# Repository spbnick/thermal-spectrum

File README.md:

Thermal Spectrum
================
Thermal Spectrum is a ZX Printer interface to a thermal printer module, for ZX
Spectrum computer.

[![Development setup][development_setup_thumb]][development_setup]

Building the firmware
---------------------
First you'll need the compiler. If you're using a Debian-based Linux you can
get it by installing `gcc-arm-none-eabi` package. Then you'll need the
[libstammer][libstammer] library. Build it first, then export environment
variables pointing to it:

    export CFLAGS=-ILIBSTAMMER_DIR LDFLAGS=-LLIBSTAMMER_DIR

`LIBSTAMMER_DIR` above is the directory where libstammer build is located.

After that you can build the firmware using `make`.

[development_setup_thumb]: development_setup.thumb.jpg
[development_setup]: development_setup.jpg
[libstammer]: https://github.com/spbnick/libstammer

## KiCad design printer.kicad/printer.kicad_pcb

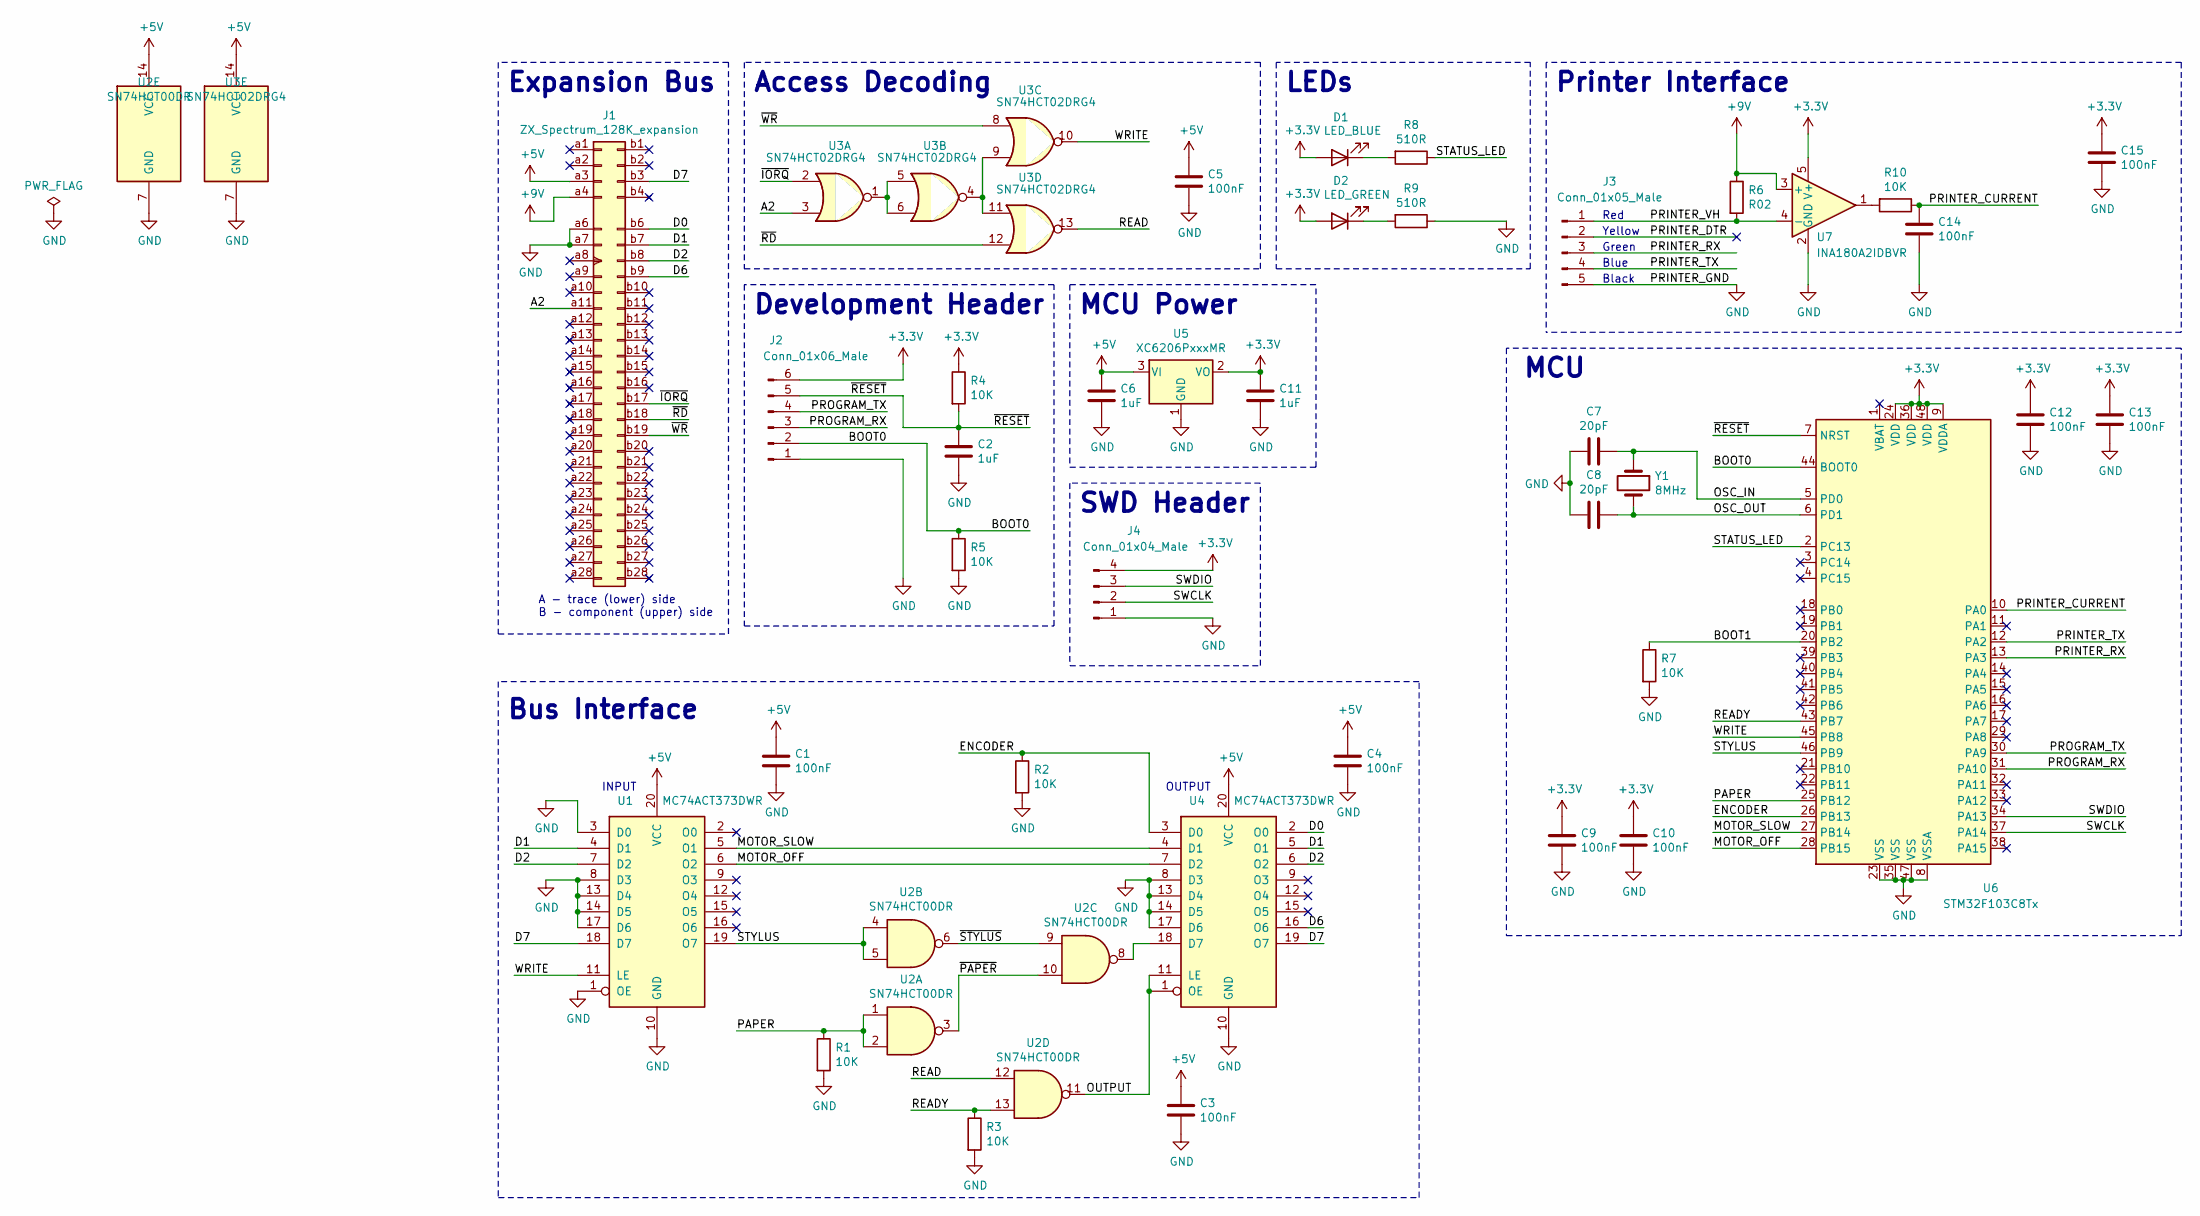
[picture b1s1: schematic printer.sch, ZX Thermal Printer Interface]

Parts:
C1, C3, C4, C5, C9, C10, C12, C13, C14, C15: 100nF; C_0603_1608Metric; LCSC C24452
C2, C6, C11: 1uF; C_0603_1608Metric; LCSC C15849
C7, C8: 20pF; C_0603_1608Metric; LCSC C1648
D1: LED_BLUE; LED_0603_1608Metric; LCSC C72041
D2: LED_GREEN; LED_0603_1608Metric; LCSC C72043
J1: ZX_Spectrum_128K_expansion; board_socket
J2: Conn_01x06_Male; PinHeader_1x06_P2.54mm_Vertical
J3: Conn_01x05_Male; JST_XH_B5B-XH-A_1x05_P2.50mm_Vertical
J4: Conn_01x04_Male; PinHeader_1x04_P2.54mm_Vertical
R1, R2, R3, R4, R5, R7: 10K; R_0603_1608Metric; LCSC C25804
R6: R02; R_1206_3216Metric; LCSC C83318
R8, R9: 510R; R_0603_1608Metric; LCSC C23193
R10: 10K; R_0603_1608Metric; LCSC C23193
U1, U4: MC74ACT373DWR; SOIC-20W_7.5x12.8mm_P1.27mm; LCSC C233456
U2: SN74HCT00DR; SOIC-14_3.9x8.7mm_P1.27mm; LCSC C6764
U3: SN74HCT02DRG4; SOIC-14_3.9x8.7mm_P1.27mm; LCSC C6765
U5: XC6206PxxxMR; SOT-23; LCSC C5446
U6: STM32F103C8Tx; LQFP-48_7x7mm_P0.5mm; LCSC C8734
U7: INA180A2IDBVR; SOT-23-5; LCSC C192764
Y1: 8MHz; Crystal_SMD_5032-2Pin_5.0x3.2mm; LCSC C156253

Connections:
+3V3: C9.1, C10.1, C11.2, C12.1, C13.1, C15.1, D1.2 (A), D2.2 (A), J2.6, J4.4, R4.1, U5.2 (VO), U6.9 (VDDA), U6.24 (VDD), U6.36 (VDD), U6.48 (VDD), U7.5 (V+)
+5V: C1.1, C3.1, C4.1, C5.1, C6.2, J1.a3 (+5V), U1.20 (VCC), U2.14 (VCC), U3.14 (VCC), U4.20 (VCC), U5.3 (VI)
+9V: J1.a4 (+9V), R6.1, U7.3 (+)
/A2: J1.a11 (A2), U3.3
/BOOT0: J2.2, R5.1, U6.44 (BOOT0)
/BOOT1: R7.1, U6.20 (PB2)
/D0: J1.b6 (D0), U4.2 (O0)
/D1: J1.b7 (D1), U1.4 (D1), U4.5 (O1)
/D2: J1.b8 (D2), U1.7 (D2), U4.6 (O2)
/D6: J1.b9 (D6), U4.16 (O6)
/D7: J1.b3 (D7), U1.18 (D7), U4.19 (O7)
/ENCODER: R2.1, U4.3 (D0), U6.26 (PB13)
/MOTOR_OFF: U1.6 (O2), U4.7 (D2), U6.28 (PB15)
/MOTOR_SLOW: U1.5 (O1), U4.4 (D1), U6.27 (PB14)
/OSC_IN: C7.1, U6.5 (PD0), Y1.1
/OSC_OUT: C8.1, U6.6 (PD1), Y1.2
/OUTPUT: U2.11, U4.1 (OE), U4.11 (LE)
/PAPER: R1.1, U2.1, U2.2, U6.25 (PB12)
/PRINTER_CURRENT: C14.1, R10.1, U6.10 (PA0)
/PRINTER_DTR: J3.2
/PRINTER_RX: J3.3, U6.13 (PA3)
/PRINTER_TX: J3.4, U6.12 (PA2)
/PRINTER_VH: J3.1, R6.2, U7.4 (-)
/PROGRAM_RX: J2.3, U6.31 (PA10)
/PROGRAM_TX: J2.4, U6.30 (PA9)
/READ: U2.12, U3.13
/READY: R3.1, U2.13, U6.43 (PB7)
/STATUS_LED: R8.1, U6.2 (PC13)
/STYLUS: U1.19 (O7), U2.4, U2.5, U6.46 (PB9)
/SWCLK: J4.2, U6.37 (PA14)
/SWDIO: J4.3, U6.34 (PA13)
/WRITE: U1.11 (LE), U3.10, U6.45 (PB8)
/~IORQ: J1.b17 (~IORQ), U3.2
/~PAPER: U2.3, U2.10
/~RD: J1.b18 (~RD), U3.12
/~RESET: C2.2, J2.5, R4.2, U6.7 (NRST)
/~STYLUS: U2.6, U2.9
/~WR: J1.b19 (~WR), U3.8
GND: C1.2, C2.1, C3.2, C4.2, C5.2, C6.1, C7.2, C8.2, C9.2, C10.2, C11.1, C12.2, C13.2, C14.2, C15.2, J1.a6 (0V), J1.a7 (0V), J2.1, J3.5, J4.1, R1.2, R2.2, R3.2, R5.2, R7.2, R9.1, U1.1 (OE), U1.3 (D0), U1.8 (D3), U1.10 (GND), U1.13 (D4), U1.14 (D5), U1.17 (D6), U2.7 (GND), U3.7 (GND), U4.8 (D3), U4.10 (GND), U4.13 (D4), U4.14 (D5), U4.17 (D6), U5.1 (GND), U6.8 (VSSA), U6.23 (VSS), U6.35 (VSS), U6.47 (VSS), U7.2 (GND)
unnamed: D1.1 (K), R8.2
unnamed: D2.1 (K), R9.2
unnamed: R10.2, U7.1
unnamed: U2.8, U4.18 (D7)
unnamed: U3.1, U3.5, U3.6
unnamed: U3.4, U3.9, U3.11

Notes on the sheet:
A - trace (lower) side B - component (upper) side
INPUT
OUTPUT
Access Decoding
Development Header
Bus Interface
MCU Power
LEDs
SWD Header
MCU
Expansion Bus
Printer Interface
Red
Yellow
Green
Blue
Black

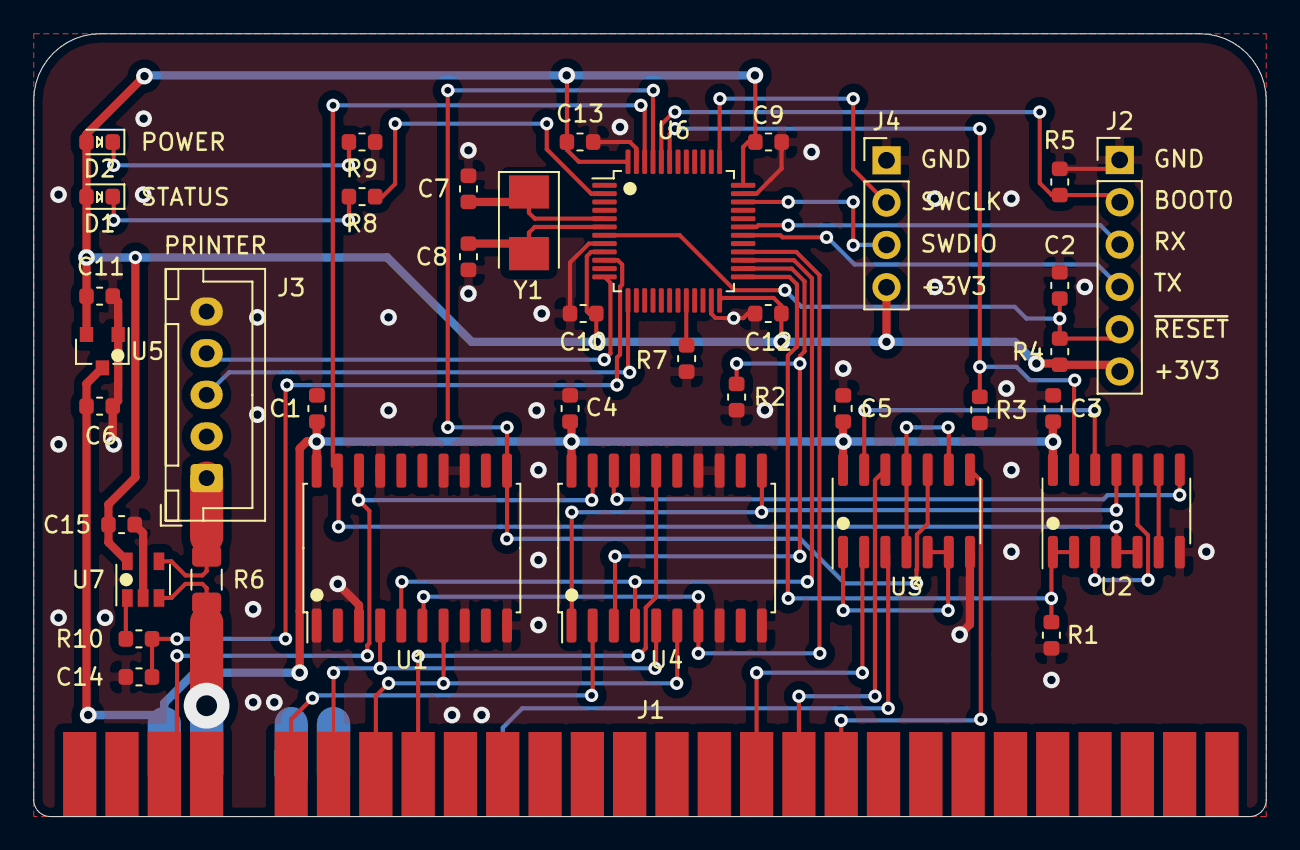
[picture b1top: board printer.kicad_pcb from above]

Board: 2 copper layers, 74.0 x 47.0 mm, 39 parts (0 on the bottom side), 44 nets.

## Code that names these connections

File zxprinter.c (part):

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{
    /* Read the pins */
    uint16_t pins = zxprinter_gpio->idr;
    uint16_t motor_off = (pins >> ZXPRINTER_PIN_MOTOR_OFF) & 1U;
    uint16_t motor_slow = (pins >> ZXPRINTER_PIN_MOTOR_SLOW) & 1U;
    /* Determine current and next clock step and level */
    uint32_t clock_level = zxprinter_clock_level;
    uint32_t next_clock_step = zxprinter_clock_step + 1;
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                            ZXPRINTER_CYCLE_MARGIN_STEPS);
            uint8_t byte = dot >> 3;
            uint8_t bit = 7 - (dot & 0x7);
            uint8_t stylus = ((pins >> ZXPRINTER_PIN_STYLUS) & 1);
            /* Record dot state */
            zxprinter_line_buf[byte] =
                (zxprinter_line_buf[byte] & ~(1 << bit)) |
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
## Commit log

2018-05-27 Add basic Makefile and dummy program
2018-05-27 Add draft serial IO
2018-05-27 Add .gitignore
2018-05-27 Rename serial_tx_ functions to serial_tx_buf_
2018-10-03 Improve wording of circular buffer description
2018-11-25 Makefile: Include dependencies
2018-11-25 Makefile: Move default target to the front
2018-11-25 Add serial module
2018-12-02 Add printer interface module
2018-12-02 Rename program to ts (thermal spectrum)
2018-12-02 Implement printing a test image on power-on
2018-12-03 Add KiCAD schematics
2018-12-03 Add README.md
2018-12-03 README.md: Refine introduction
2018-12-03 README.md: Move links to the back
2018-12-03 README.md: Fix libstammer link
2019-01-06 Reimplement ZX Spectrum bus interface
2019-01-06 Add draft ZX Printer bus interface implementation
2019-01-06 Remove trailing whitespace from zxprinter.c
2019-01-06 Add notes.txt
2019-08-17 Redo latching in HW, understand interface better
    Redo latching in hardware, only to understand after testing that the
    interface is different. The printer is supposed to reset the latches on
    every write regardless of the encoder and paper position.
2019-08-31 Make ZX Printer communication work
2019-08-31 Use external line buffer in ZX Printer interface
2019-11-03 Make the interface work
2019-12-08 Complete schematics for JLCPCB
2019-12-08 Fix unconnected resistors on schematics
2019-12-08 Shorten SN74HCT00PWR to SN74HCT00
2019-12-22 Start laying out the PCB
2019-12-25 Fix symbol library path
2019-12-27 Add kicad-symbols submodule
2019-12-28 Add linear regulator symbol library from KiCAD master
2019-12-28 Remove printer-cache use from schematics
2019-12-28 Do not connect to the separate ground pin on the bus
2019-12-28 Route all bus signal pins and some chip connections
2019-12-28 Route all internal connections for interface chips
2019-12-28 Remove debug serial
2019-12-28 Layout MCU surroundings roughly
2019-12-28 Remove oscillator load resistor
2019-12-30 Reverse pins on dev connector
2019-12-30 Do most of the layout without ground fill
2019-12-30 Remove all ground tracks
2019-12-31 Routed all connections, with ground fill
2019-12-31 Tidy up a bit
2019-12-31 Center edge pads comment
2019-12-31 Add thicker connection of the ground plane
2020-01-01 Add unconnected copper pour to top side
2020-01-02 Add polarity marks to top silkscreen
2020-01-02 Add banner and JLCPCB number placeholder
2020-01-03 Switch to parts in stock at LCSC
2020-01-03 Label OUTPUT net
2020-01-03 Reroute with new footprints and top ground fill
2020-01-03 Improve ground connectivity and reduce loops
2020-01-03 Refine silkscreen and fab comments
2020-01-05 Add production .csv and .xml files to .gitignore
2020-01-05 Generate gerbers and production files
2020-01-17 Remove setup of unused debug GPIO and USART
2020-01-17 Document printer configuration parameters
2020-01-17 Implement status LED output
2020-01-17 Reset printer on init
2020-05-08 schematics: Add printer current sensing
2020-05-08 printer: Remove reset after config
2020-05-08 Remove test image
2020-05-08 Move status LED config to printer section
2020-05-09 Rename printer_handler() to printer_tim_handler()
    Rename printer_handler() to printer_tim_handler() to distinguish it from
    the future ADC interrupt handler.
2020-06-02 Straighten printer peripheral init order
2020-06-21 Switch to flow control by printer current consumption
2020-06-21 printer: Increase contrast
2020-06-27 Switch to in-stock LCSC latches
2020-06-30 Add bypass cap for current sense amp
2020-07-04 Reroute PCB to accommodate new circuits
2020-07-04 Set options for JLCPCB production export
2020-09-26 Link with gcc to use its functions
2020-09-26 Remove unused circular_buf and serial modules
